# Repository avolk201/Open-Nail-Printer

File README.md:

# Open-Source Inkjet Nail Printer

## Overview
This repository contains the hardware schematics, firmware, and software required to build a custom, desktop-scale inkjet nail printer. The system utilizes a standard thermal inkjet (TIJ) cartridge (HP 63) to deposit water-based cosmetic/edible ink directly onto a prepared human nail. 

Unlike commercial alternatives that rely on closed-source hardware and DRM-locked consumables, this project provides a fully open architecture. It uses a distributed processing model, offloading high-level computer vision and web serving to a Raspberry Pi, while delegating strict, microsecond-accurate hardware control to an ESP32 microcontroller utilizing I2S Direct Memory Access (DMA).

## System Architecture

The project is divided into three distinct operational domains:

### 1. High-Level Processing (Raspberry Pi 3B+)
* **Environment:** Python 3, FastAPI, OpenCV.
* **Function:** Operates in a headless kiosk mode serving a React/Vue frontend to a local touchscreen UI. 
* **Vision Pipeline:** Captures the finger via a fixed-focus, low-distortion downward-facing camera. Allows the user to define a bounding box, warps the selected 2D image using a 1D sine-wave pre-distortion algorithm to map to the nail's curvature, and converts the RGB image into a binary CMYK halftone matrix via Floyd-Steinberg error diffusion.
* **Communication:** Slices the halftone matrix into 42-byte chunks and transmits them via UART over USB to the ESP32 at 921,600 baud.

### 2. Real-Time Hardware Control (ESP32)
* **Environment:** ESP-IDF (C), FreeRTOS.
* **Core 0:** Dedicated to receiving UART payloads and buffering them into FreeRTOS queues.
* **Core 1:** Manages electromechanical synchronization. Triggers the I2S DMA peripheral to output perfectly timed 5µs pulses across 12 parallel GPIO pins without CPU blocking. 
* **Motion Control:** Interfaces with TMC2209 stepper drivers for silent, vibration-free gantry movement, utilizing a linear optical encoder and hardware pulse counting (PCNT) for absolute microscopic positional accuracy.

### 3. Custom PCB & Power Distribution
The electrical architecture is split across two custom KiCad boards to ensure signal integrity and isolate high voltages:
* **Stationary Mainboard:** Houses the ESP32, TMC2209 drivers, and the central Power Distribution Network (PDN). It steps a 24V DC input down to 16V (Printhead), 9V (Logic Leveling), and 5V (Raspberry Pi/ESP32 supply).
* **Smart Carriage:** A lightweight, moving PCB connected via a Flexible Flat Cable (FFC). It houses CD4504B CMOS level shifters to step 3.3V data lines to 9V, and a custom P-Channel/N-Channel discrete MOSFET array to switch 16V firing pulses millimeters away from the cartridge's pogo-pin interface, eliminating inductive ringing.

## Safety & Hardware Interlocks
A critical feature of this design is the hardware "guillotine" failsafe located on the Smart Carriage. 

Thermal inkjet resistors will permanently burn out if held high for more than a few microseconds. To protect against software lockups, the 16V firing lines are routed through an AC-coupled gate drive (capacitive differentiator). An RC time-constant enforces a strict physical timeout of approximately 10-15µs. If the ESP32 freezes while a firing pin is pulled high, the capacitor will charge and autonomously sever the 16V supply to the cartridge, preventing thermal runaway.

## Repository Structure

* `/cad`: (In Progress) Onshape mechanical assemblies, STL files, and 3D printable carriage mounts.
* `/Nail-printer-embedded`: ESP-IDF C source code and FreeRTOS task configurations.
* `/NailPrinter_PCB`: KiCad 8.0 project files, library symbols, and footprints.
## Project Status

### Completed Features
* **Backend (Raspberry Pi)**
    * FastAPI server architecture with REST endpoints for system control and design management.
    * Computer Vision pipeline: Floyd-Steinberg halftoning (RGB to CMYK), 1D sine-wave nail warping, and manual affine transformations.
    * High-speed UART serial protocol (921,600 baud) for ESP32 communication.
    * MJPEG camera streaming for real-time nail alignment.
* **Frontend (Touchscreen UI)**
    * Vue 3/Vite application optimized for 7" Raspberry Pi touchscreen.
    * Interactive alignment interface with manual bounding box selection.
    * Real-time design adjustment (scale, rotation, pan) via overlay.
    * Design gallery and "Set" printing workflow for sequential multi-finger printing.
* **Firmware (ESP32)**
    * Dual-core task distribution: UART ingestion on Core 0, motion/sync on Core 1.
    * I2S Parallel DMA driver for microsecond-accurate HP 63 cartridge firing.
    * TMC2209 stepper driver integration via UART and MCPWM pulse generation.
    * Hardware pulse counting (PCNT) infrastructure for linear optical encoder feedback.
* **Hardware (KiCad)**
    * Two-board architecture: Stationary Mainboard and Smart Carriage.
    * Power distribution for 24V, 16V (firing), 9V (logic), and 5V (MCU) rails.
    * Hardware guillotine failsafe using capacitive AC-coupling.

### Pending / TODO
* **Firmware**
    * Implement hardware-level trigger linking PCNT encoder thresholds to I2S DMA output for closed-loop positional accuracy.
    * Complete homing sequence logic within limit switch ISR handlers.
    * Implement S-curve acceleration ramps for smoother gantry motion.
* **Backend**
    * Replace OpenCV camera capture with native `libcamera` or `picamera2` for Raspberry Pi hardware.
    * Implement automated nail segmentation to replace manual bounding box alignment.
* **Hardware**
    * Verify and resolve 9V/3.3V domain crossing alerts in schematic.
    * Add fiducial markers for automated pick-and-place assembly.
    * Populate manufacturer part numbers (MPNs) across the Bill of Materials.
* **Mechanics**
    * Finalize and release Onshape CAD assemblies and 3D printable STL files for the gantry and carriage.

## Development Milestones

1.  **Software**: Implementation of the FastAPI server, Vue UI, and CMYK halftoning pipeline. [DONE]
2.  **Hardware Design**: Design and layout of the Mainboard and Smart Carriage PCBs. [DONE]
3.  **Hardware Validation**: Manufacture PCBs and confirm functional operation. [TODO]
4.  **Firmware Core**: High-speed communication and raw I2S printhead driving. [DONE]
5.  **Motion Control Integration**: Synchronization of gantry movement with firmware step generation. [IN PROGRESS]
6.  **Closed-Loop Accuracy**: Linking linear optical encoder pulses to hardware-triggered ink deposition. [TODO]
7.  **Kiosk Mode Integration**: Final Raspberry Pi OS configuration for standalone touchscreen operation. [TODO]
8.  **System Validation**: Full 5-finger print test using water-based cosmetic ink. [TODO]

### Prerequisites
* Raspberry Pi OS Lite (64-bit)
* Espressif ESP-IDF v5.x
* KiCad 8.0+
* 24V 3A DC Power Supply
* Modified HP 63 Tri-Color Cartridge (Flushed and refilled with water-based cosmetic/edible ink).

### Software Setup
1. Clone the repository to the Raspberry Pi.
2. Navigate to `backend/` and install dependencies: `pip install -r requirements.txt`.
3. Configure the Pi to launch the FastAPI server on boot.
4. Flash the ESP32 firmware: `idf.py build flash monitor`.

## License
This project is licensed under the MIT License. See the `LICENSE` file for details. Note that any proprietary modifications to the HP 63 cartridge footprint are for educational and research purposes only.

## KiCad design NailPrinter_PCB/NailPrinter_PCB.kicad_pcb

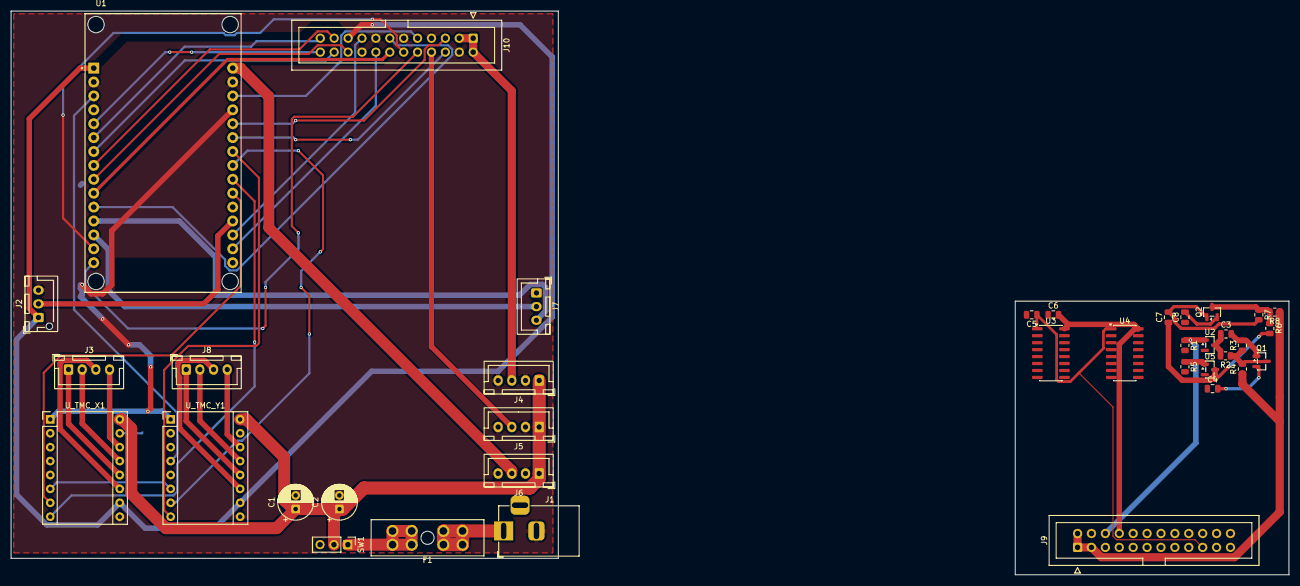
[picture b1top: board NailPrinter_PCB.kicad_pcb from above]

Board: 2 copper layers, 233.5 x 103.0 mm, 37 parts (0 on the bottom side), 47 nets.

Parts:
C1, C2: 100uF; CP_Radial_D6.3mm_P2.50mm
C3, C4, C7, C8: 10n; C_0805_2012Metric
C5, C6: 100n; C_0805_2012Metric
F1: Fuse; FuseHolder_Blade_ATO_Littelfuse_FLR_178.6165
J1: Barrel_Jack; BarrelJack_Horizontal
J2: Conn_01x03; JST_XH_B3B-XH-AM_1x03_P2.50mm_Vertical
J3, J4, J5, J6, J8: Conn_01x04; JST_XH_B4B-XH-A_1x04_P2.50mm_Vertical
J7: Conn_01x03; JST_XH_B3B-XH-A_1x03_P2.50mm_Vertical
J9, J10: Conn_01x24; IDC-Header_2x12_P2.54mm_Vertical
Q1, Q2: AO3401; SOT-23
R1, R5: 10k; R_0805_2012Metric
R2, R3, R6, R7: 1k; R_0805_2012Metric
R4, R8: 2.7; R_0805_2012Metric
SW1: SW_SPST; PinHeader_1x03_P2.54mm_Vertical
U1: DEVKIT_V1_ESP32-WROOM-32; MODULE_DEVKIT_V1_ESP32-WROOM-32
U2, U5: AO3400; SOT-23
U3, U4: CD4504BM; SOIC-16_3.9x9.9mm_P1.27mm
U_TMC_X1: BTT_TMC2209_V1.2; Pololu_Breakout-16_15.2x20.3mm
U_TMC_Y1: BTT_TMC2209_V1.2; Pololu_Breakout-16_15.2x20.3mm

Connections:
+3.3V: C5.1, J2.1, J9.19, J10.19, U1.1 (3V3), U3.1 (VCC), U4.1 (VCC), U_TMC_X1.10 (VIO), U_TMC_Y1.10 (VIO)
+5V: J6.3, U1.30 (EXT_5V)
+9V: C6.2, J5.3, J9.8, J10.8, U3.16 (VDD), U4.16 (VDD)
+16V: J4.3, J9.1, J9.2, J9.3, J10.1, J10.2, J10.3, R4.1, R8.1
+24V: C1.1, C2.1, J4.1, J5.1, J6.1, SW1.2 (B), U_TMC_X1.16 (VM), U_TMC_Y1.16 (VM)
CLK_3V: J10.10, U1.15 (IO23), U3.7 (CIN)
D1_3V: J10.12, U1.14 (IO22), U3.11 (EIN)
D2_3V: J10.13, U1.11 (IO21), U3.5 (BIN)
D3_3V: J10.14, U1.10 (IO19), U3.9 (DIN)
D4_3V: J10.20, U1.9 (IO18), U3.14 (FIN)
D5_3V: J10.21, U1.8 (IO5), U4.3 (AIN)
D6_3V: J10.22, U1.7 (IO17), U4.5 (BIN)
D7_3V: J10.23, U1.6 (IO16), U4.7 (CIN)
D8_3V: J10.24, U1.5 (IO4), U4.9 (DIN)
DIR_X: U1.22 (IO33), U_TMC_X1.8 (DIR)
DIR_Y: U1.24 (IO26), U_TMC_Y1.8 (DIR)
ENC_A: J9.16, J10.16, U1.17 (SENSOR_VP)
ENC_B: J9.17, J10.17, U1.18 (SENSOR_VN)
ENDSTOP_X: J2.2, U1.19 (IO34)
EN_MOTORS: U1.27 (IO12), U_TMC_X1.1 (EN), U_TMC_Y1.1 (EN)
GND: C1.2, C2.2, C4.1, C5.2, C6.1, C8.1, J1.2, J2.3, J4.2, J4.4, J5.2, J5.4, J6.2, J6.4, J7.1, J9.4, J9.7, J9.11, J9.15, J9.18, J10.4, J10.7, J10.11, J10.15, J10.18, R1.2, R5.2, U1.2 (GND1), U1.29 (GND2), U2.2, U3.8 (VSS), U3.13 (SELECT), U4.8 (VSS), U4.11 (EIN), U4.13 (SELECT), U4.14 (FIN), U5.2, U_TMC_X1.9 (GND), U_TMC_X1.15 (GND), U_TMC_Y1.9 (GND), U_TMC_Y1.15 (GND)
unnamed: C3.1, R2.2, U2.3
unnamed: C3.2, Q1.1, R3.2
unnamed: C7.1, R6.2, U5.3
unnamed: C7.2, Q2.1, R7.2
unnamed: F1.1, J1.1
unnamed: J3.1, U_TMC_X1.12 (OA1)
unnamed: J3.2, U_TMC_X1.13 (OA2)
unnamed: J3.3, U_TMC_X1.11 (OB1)
unnamed: J3.4, U_TMC_X1.14 (OB2)
unnamed: J7.2, U1.13 (TXD0)
unnamed: J7.3, U1.12 (RXD0)
unnamed: J8.1, U_TMC_Y1.12 (OA1)
unnamed: J8.2, U_TMC_Y1.13 (OA2)
unnamed: J8.3, U_TMC_Y1.11 (OB1)
unnamed: J8.4, U_TMC_Y1.14 (OB2)
unnamed: Q1.3, R2.1, R3.1, R4.2
unnamed: Q2.3, R6.1, R7.1, R8.2
unnamed: F1.2, SW1.1 (A)
PWRA_IN: J9.6, J10.6, R1.1, U1.25 (IO27), U2.1
PWRA_OUT: C4.2, Q1.2
PWRB_IN: J9.5, J10.5, R5.1, U1.26 (IO14), U5.1
PWRB_OUT: C8.2, Q2.2
STEP_X: U1.21 (IO32), U_TMC_X1.7 (STEP)
STEP_Y: U1.23 (IO25), U_TMC_Y1.7 (STEP)
SYNC_3V: J10.9, U1.28 (IO13), U3.3 (AIN)
UART_Y: U1.3 (IO15), U_TMC_Y1.4 (PDN/UART1)

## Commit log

2026-04-24 Website mockup
2026-04-24 Added upload/gallery features
2026-04-24 added a test file and a script to start the server
2026-04-24 stop server script
2026-04-24 edited the server scripts and began pcb design
2026-04-25 updated start_server to include frontend
2026-04-25 autostart wasn't configured fully
2026-04-25 added embedded c code (based on https://github.com/Spritetm/printercart_simple/tree/master)
2026-04-25 tuning start_server.sh
2026-04-25 still debugging autostart
2026-04-25 Beginning PCB Design and ReadMe
2026-04-25 Added acknowledgement section
2026-04-25 Edited readme to reflect project structure
2026-04-26 mostly schematic and pcb design
2026-04-26 Placed components on pcb
2026-04-26 Preliminary traces, probably needs a lot more tweaking
2026-04-30 Added TODO list to readme. Routed Mainboard PCB
2026-05-07 Adjusting traces for the sake of signal integrity
